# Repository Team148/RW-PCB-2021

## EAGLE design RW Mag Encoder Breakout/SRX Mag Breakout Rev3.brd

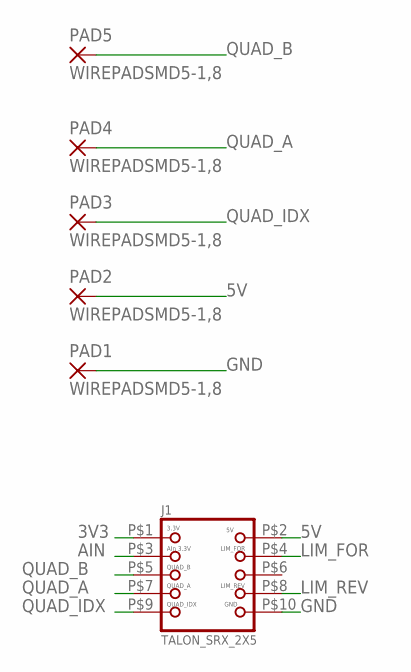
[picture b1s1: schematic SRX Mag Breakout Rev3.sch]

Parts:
J1: TALON_SRX_2X5; 2X5-0.05-HEADER
PAD1, PAD2, PAD3, PAD4, PAD5: WIREPADSMD5-1,8; 5-1,8

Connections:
3V3: J1.P$1 (1)
5V: J1.P$2 (2), PAD2.1
AIN: J1.P$3 (3)
GND: J1.P$10 (10), PAD1.1
LIM_FOR: J1.P$4 (4)
LIM_REV: J1.P$8 (8)
QUAD_A: J1.P$7 (7), PAD4.1
QUAD_B: J1.P$5 (5), PAD5.1
QUAD_IDX: J1.P$9 (9), PAD3.1

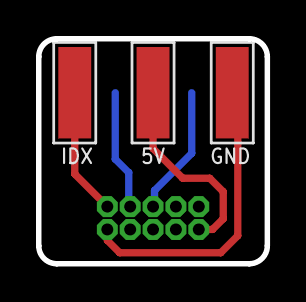
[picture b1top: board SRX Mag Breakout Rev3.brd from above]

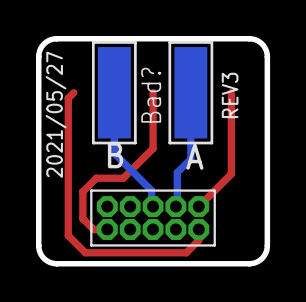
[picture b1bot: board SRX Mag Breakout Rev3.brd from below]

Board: 2 copper layers, 12.7 x 12.5 mm, 6 parts (3 on the bottom side), 5 nets.

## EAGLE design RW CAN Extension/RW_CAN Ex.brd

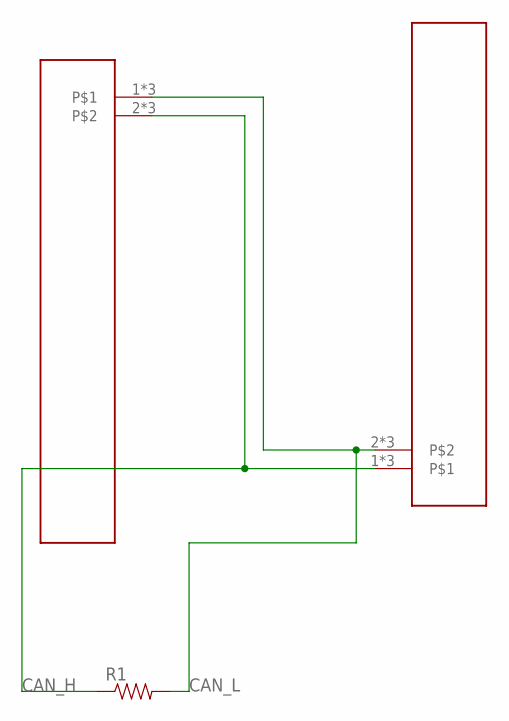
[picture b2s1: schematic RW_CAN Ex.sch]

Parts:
R1: RESISTOR1206; 1206
U$2, U$3: WEIDMULLERLSF-3_50-2-90; LSF_2_90

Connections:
CAN_H: R1.1, U$2.2, U$2.12, U$2.22, U$3.1, U$3.11, U$3.21
CAN_L: R1.2, U$2.1, U$2.11, U$2.21, U$3.2, U$3.12, U$3.22

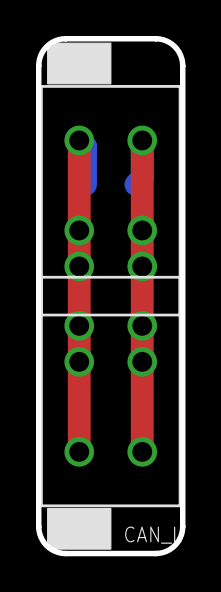
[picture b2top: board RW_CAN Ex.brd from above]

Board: 2 copper layers, 8.0 x 28.6 mm, 3 parts (1 on the bottom side), 2 nets.

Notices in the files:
parts and their libraries:
SparkFun-Passives: Licensing: CC v3.0 Share-Alike You are welcome to use this library for commercial purposes.
